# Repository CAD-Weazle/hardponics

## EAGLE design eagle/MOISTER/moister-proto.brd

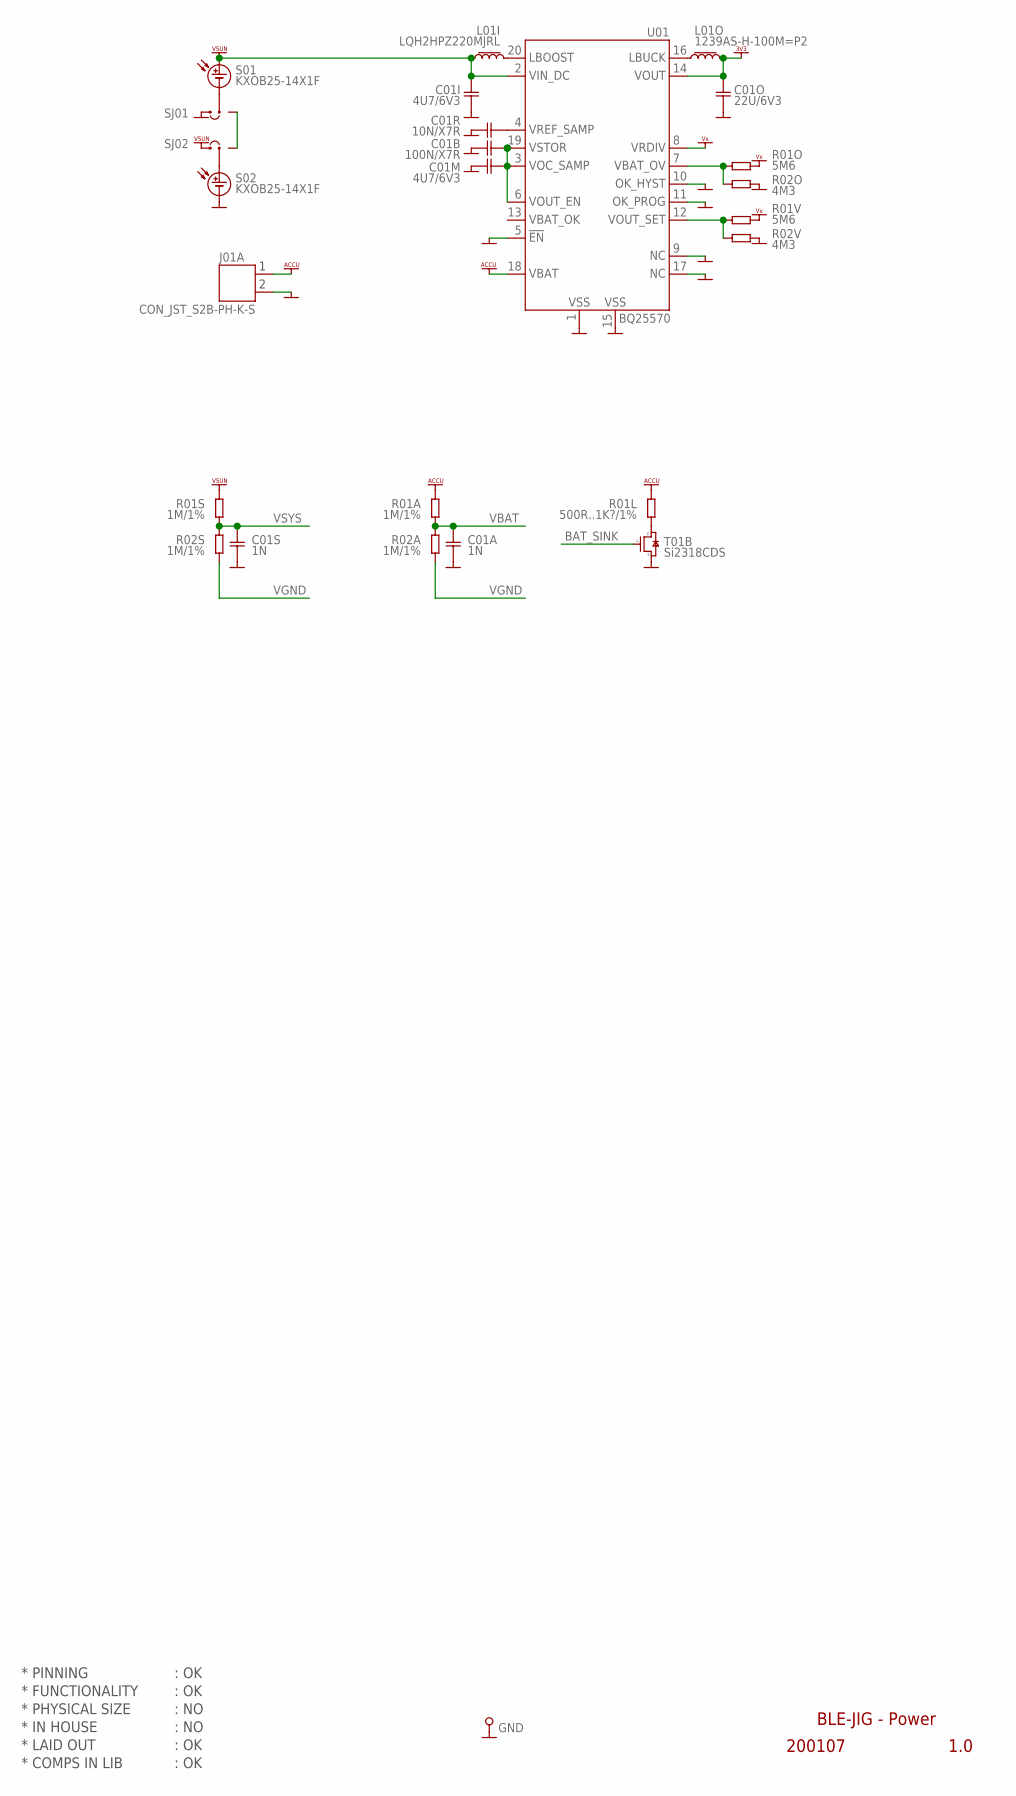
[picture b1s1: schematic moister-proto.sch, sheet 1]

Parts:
C01A, C01S: 1N; CAP0402
C01B: 100N/X7R; CAP0402
C01I, C01M: 4U7/6V3; CAP0402
C01O: 22U/6V3; CAP0402
C01R: 10N/X7R; CAP0402
GND: PIN_TEST; HOLE_PTH_0.8MM
J01A: CON_JST_S2B-PH-K-S
L01I: LQH2HPZ220MJRL; L_1008
L01O: 1239AS-H-100M=P2; L_1008
R01A, R01S, R02A, R02S: 1M/1%; RES0402
R01L: 500R..1K?/1%; RES0603
R01O, R01V: 5M6; RES0402
R02O, R02V: 4M3; RES0402
S01, S02: KXOB25-14X1F
SJ01, SJ02: SJ3SJ3-S; SJ3-S
T01B: Si2318CDS; NFET_SOT23
U01: BQ25570; VQFN20

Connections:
ACCU: J01A.1, R01A.2, R01L.2, U01.18 (18.VBAT)
BAT_SINK: T01B.1 (G1); also elsewhere on the board
GND: C01A.2, C01B.2, C01I.2, C01M.2, C01O.2, C01R.2, C01S.2, GND.1, J01A.2, R02O.2, R02V.2, S02.2, SJ01.1, T01B.2 (S2), U01.1 (1.VSS), U01.5 (5.!EN), U01.9 (9.NC), U01.10 (10.OK_HYST), U01.11 (11.OK_PROG), U01.15 (15.VSS), U01.17 (17.NC), U01.TP (15.VSS), U01.V1 (15.VSS), U01.V2 (15.VSS), U01.V3 (15.VSS), U01.V4 (15.VSS); also elsewhere on the board
unnamed: S01.2, SJ01.2
unnamed: S02.1, SJ02.2
unnamed: SJ01.3, SJ02.3
unnamed: R01L.1, T01B.3 (D3)
unnamed: C01R.1, U01.4 (4.VREF_SAMP)
unnamed: L01I.2, U01.20 (20.LBOOST)
unnamed: L01O.1, U01.16 (16.LBUCK)
VBAT: C01A.1, R01A.1, R02A.2; also elsewhere on the board
VBAT_OV: R01O.2, R02O.1, U01.7 (7.VBAT_OV)
VDD_3V3: C01O.1, L01O.2, U01.14 (14.VOUT); also elsewhere on the board
VGND: R02A.1, R02S.1; also elsewhere on the board
VOUT_SET: R01V.2, R02V.1, U01.12 (12.VOUT_SET)
VSTOR: C01B.1, C01M.1, U01.3 (3.VOC_SAMP), U01.6 (6.VOUT_EN), U01.19 (19.VSTOR)
VSUN: C01I.1, L01I.1, R01S.2, S01.1, SJ02.1, U01.2 (2.VIN_DC)
VSYS: C01S.1, R01S.1, R02S.2; also elsewhere on the board
VX: R01O.1, R01V.1, U01.8 (8.VRDIV)

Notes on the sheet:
* PINNING
* FUNCTIONALITY
* PHYSICAL SIZE
* LAID OUT
* COMPS IN LIB
* IN HOUSE
BLE-JIG - Power
200107
1.0
: OK
: NO

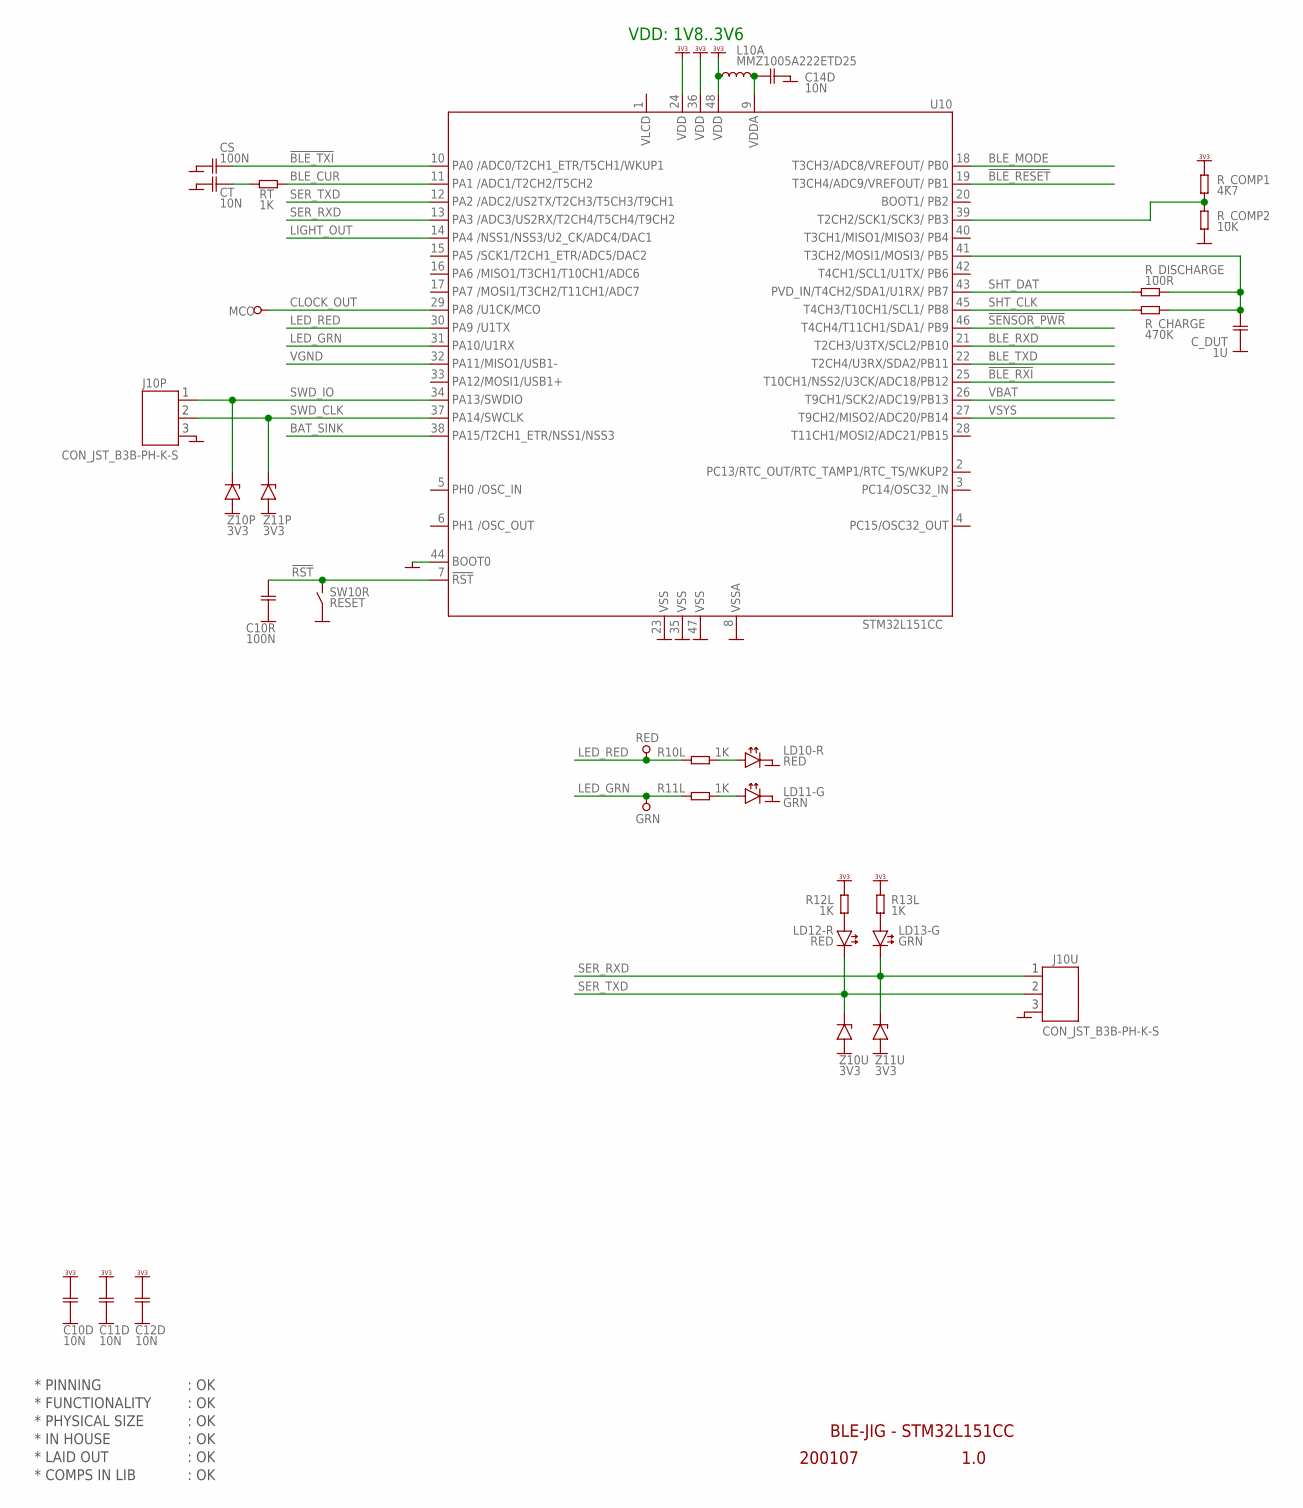
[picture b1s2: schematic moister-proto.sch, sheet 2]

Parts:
C10D, C11D, C12D, C14D: 10N; CAP0402
C10R: 100N; CAP0402
CS: 100N; CAP0805
CT: 10N; CAP0805
C_DUT: 1U; CAP0603
GRN: PIN_TEST_0.6MM; HOLE_PTH_0.6MM
J10P, J10U: CON_JST_B3B-PH-K-S
L10A: MMZ1005A222ETD25; L_0402
LD10-R, LD12-R: RED; LED_SMD_0603
LD11-G, LD13-G: GRN; LED_SMD_0603
MCO: PIN_TEST; HOLE_PTH_0.8MM
R10L, R11L, R12L, R13L: 1K; RES0402
RED: PIN_TEST_0.6MM; HOLE_PTH_0.6MM
RT: 1K; RES0805
R_CHARGE: 470K; RES0603
R_COMP1: 4K7; RES0603
R_COMP2: 10K; RES0603
R_DISCHARGE: 100R; RES0603
SW10R: RESET; SWITCH_PUSHBUTTON_EVP-AVAA1A
U10: STM32L151CC; LQFP48
Z10P, Z10U, Z11P, Z11U: 3V3; ZENER_SOD80

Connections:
!BLE_RESET: U10.19 (19.PB1); also elsewhere on the board
!BLE_RXI: U10.25 (25.PB12); also elsewhere on the board
!BLE_TXI: CS.2, U10.10 (10.PA0); also elsewhere on the board
!RST: C10R.1, SW10R.1 (1-2), U10.7 (7.!RST)
!SENSOR_PWR: U10.46 (46.PB9); also elsewhere on the board
BAT_SINK: U10.38 (38.PA15); also elsewhere on the board
BLE_CUR: RT.1, U10.11 (11.PA1); also elsewhere on the board
BLE_MODE: U10.18 (18.PB0); also elsewhere on the board
BLE_RXD: U10.21 (21.PB10); also elsewhere on the board
BLE_TXD: U10.22 (22.PB11); also elsewhere on the board
CLOCK_OUT: MCO.1, U10.29 (29.PA8)
COMP+: C_DUT.1, R_CHARGE.2, R_DISCHARGE.2, U10.41 (41.PB5)
COMP-: R_COMP1.2, R_COMP2.1, U10.39 (39.PB3)
GND: C10D.2, C10R.2, C11D.2, C12D.2, C14D.2, CS.1, CT.1, C_DUT.2, J10P.3, J10U.3, LD10-R.C, LD11-G.C, R_COMP2.2, SW10R.2 (3-4), U10.8 (8.GND), U10.23 (23.GND), U10.35 (35.GND), U10.44 (44.BOOT0), U10.47 (47.GND), Z10P.1 (A), Z10U.1 (A), Z11P.1 (A), Z11U.1 (A); also elsewhere on the board
LED_GRN: GRN.1, R11L.1, U10.31 (31.PA10)
LED_RED: R10L.1, RED.1, U10.30 (30.PA9)
LIGHT_OUT: U10.14 (14.PA4); also elsewhere on the board
unnamed: CT.2, RT.2
unnamed: LD13-G.A, R13L.2
unnamed: LD12-R.A, R12L.2
unnamed: LD11-G.A, R11L.2
unnamed: LD10-R.A, R10L.2
SER_RXD: J10U.1, LD13-G.C, U10.13 (13.PA3), Z11U.2 (C)
SER_TXD: J10U.2, LD12-R.C, U10.12 (12.PA2), Z10U.2 (C)
SHT_CLK: R_CHARGE.1, U10.45 (45.PB8); also elsewhere on the board
SHT_DAT: R_DISCHARGE.1, U10.43 (43.PB7); also elsewhere on the board
SWD_CLK: J10P.2, U10.37 (37.PA14), Z11P.2 (C)
SWD_IO: J10P.1, U10.34 (34.PA13), Z10P.2 (C)
VBAT: U10.26 (26.PB13); also elsewhere on the board
VDDA: C14D.1, L10A.2, U10.9 (9.VDD)
VDD_3V3: C10D.1, C11D.1, C12D.1, L10A.1, R12L.1, R13L.1, R_COMP1.1, U10.24 (24.VDD), U10.36 (36.VDD), U10.48 (48.VDD); also elsewhere on the board
VGND: U10.32 (32.PA11); also elsewhere on the board
VSYS: U10.27 (27.PB14); also elsewhere on the board

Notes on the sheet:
* PINNING
* FUNCTIONALITY
* PHYSICAL SIZE
* LAID OUT
* COMPS IN LIB
* IN HOUSE
: OK
BLE-JIG - STM32L151CC
200107
1.0
VDD: 1V8..3V6

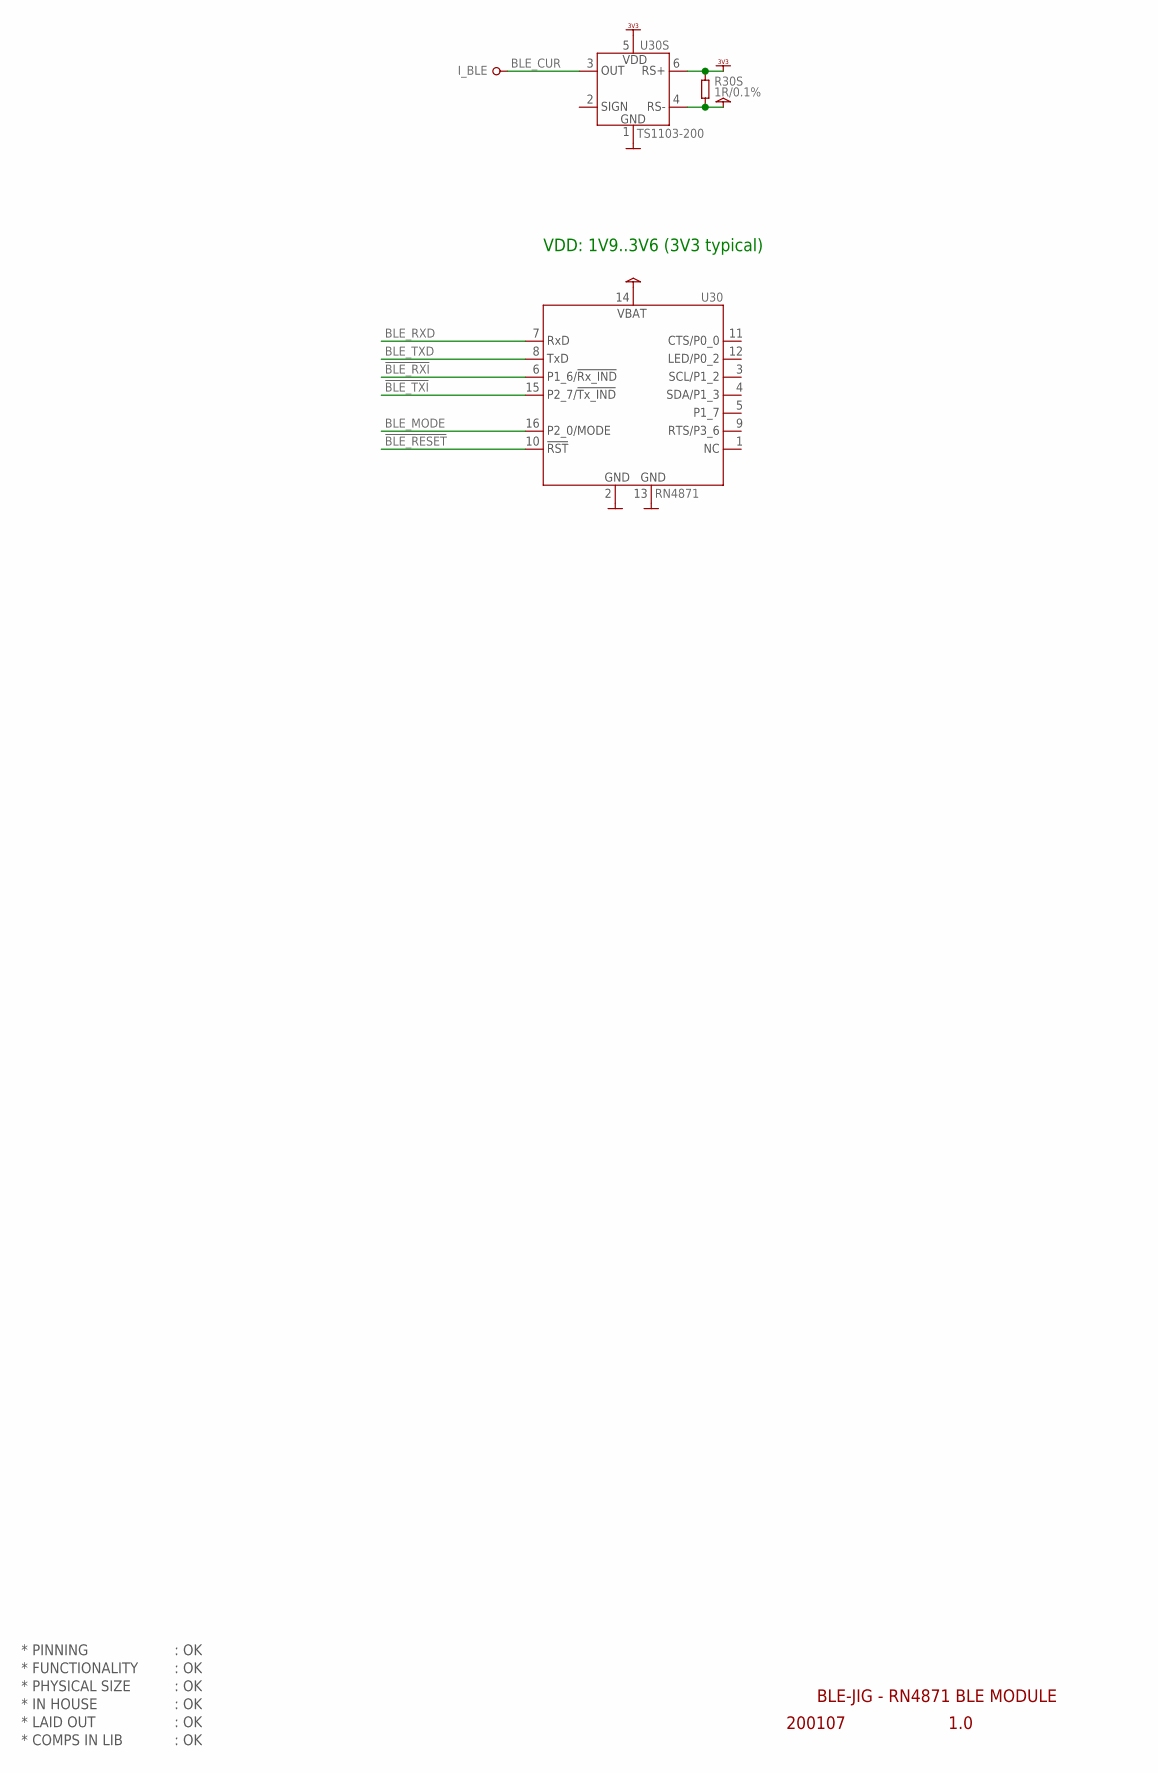
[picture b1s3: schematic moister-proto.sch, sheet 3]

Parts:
I_BLE: PIN_TEST; HOLE_PTH_0.8MM
R30S: 1R/0.1%; RES0603
U30: RN4871
U30S: TS1103-200; SOT23-6

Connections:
!BLE_RESET: U30.10 (10.!RST); also elsewhere on the board
!BLE_RXI: U30.6 (6.P1_6); also elsewhere on the board
!BLE_TXI: U30.15 (15.P2_7); also elsewhere on the board
BLE_CUR: I_BLE.1, U30S.3 (3.OUT); also elsewhere on the board
BLE_MODE: U30.16 (16.P2_0); also elsewhere on the board
BLE_RXD: U30.7 (7.RXD); also elsewhere on the board
BLE_TXD: U30.8 (8.TXD); also elsewhere on the board
GND: U30.2 (2.GND), U30.13 (13.GND), U30S.1 (1.GND); also elsewhere on the board
VCC: R30S.2, U30.14 (14.VBAT), U30S.4 (4.RS-)
VDD_3V3: R30S.1, U30S.5 (5.VDD), U30S.6 (6.RS+); also elsewhere on the board

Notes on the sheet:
* PINNING
* FUNCTIONALITY
* PHYSICAL SIZE
* LAID OUT
* COMPS IN LIB
* IN HOUSE
1.0
BLE-JIG - RN4871 BLE MODULE
200107
: OK
VDD: 1V9..3V6 (3V3 typical)

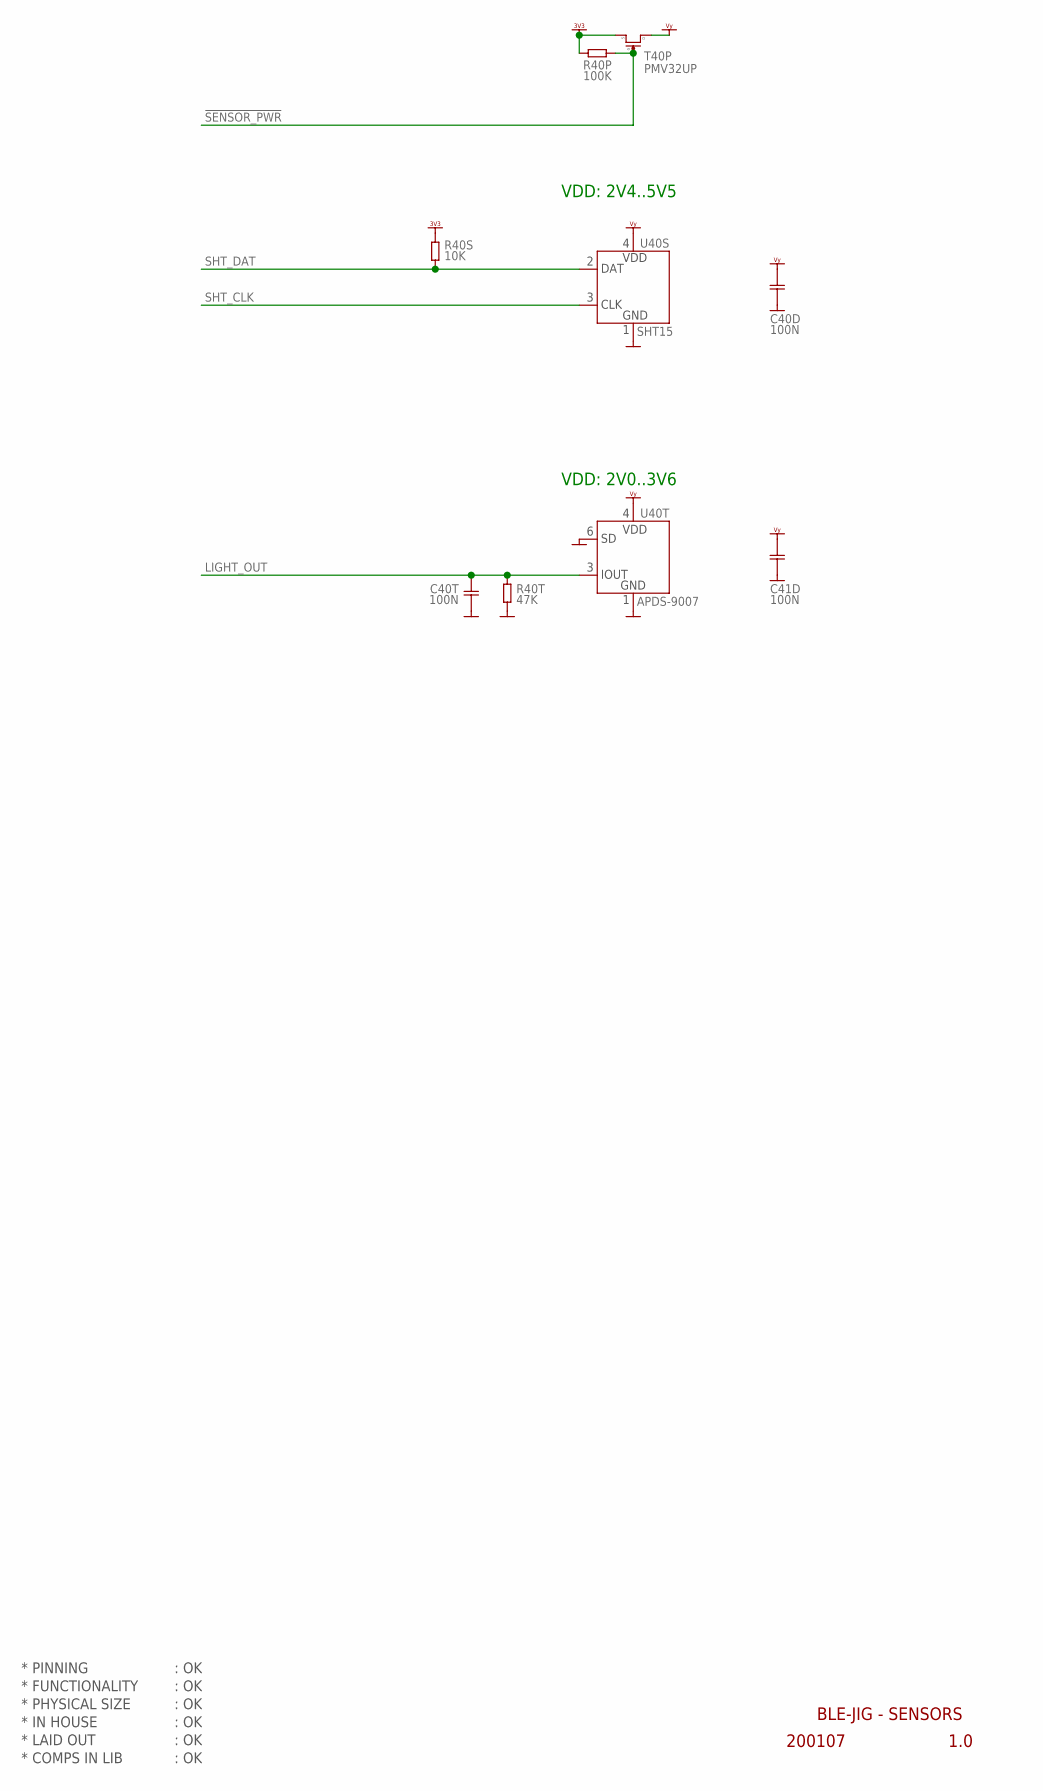
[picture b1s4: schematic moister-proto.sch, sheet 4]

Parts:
C40D, C40T, C41D: 100N; CAP0402
R40P: 100K; RES0402
R40S: 10K; RES0402
R40T: 47K; RES0402
T40P: PMV32UP; PFET_SOT23
U40S: SHT15
U40T: APDS-9007

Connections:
!SENSOR_PWR: R40P.2, T40P.1 (G); also elsewhere on the board
GND: C40D.2, C40T.2, C41D.2, R40T.2, U40S.1 (1.GND), U40T.1 (1.GND), U40T.6 (6.SD); also elsewhere on the board
LIGHT_OUT: C40T.1, R40T.1, U40T.3 (3.IOUT); also elsewhere on the board
SHT_CLK: U40S.3 (3.CLK); also elsewhere on the board
SHT_DAT: R40S.2, U40S.2 (2.DAT); also elsewhere on the board
VDD_3V3: R40P.1, R40S.1, T40P.2 (S); also elsewhere on the board
VY: C40D.1, C41D.1, T40P.3 (D), U40S.4 (4.VDD), U40T.4 (4.VDD)

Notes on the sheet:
* PINNING
* FUNCTIONALITY
* PHYSICAL SIZE
* LAID OUT
* COMPS IN LIB
* IN HOUSE
1.0
BLE-JIG - SENSORS
200107
: OK
VDD: 2V0..3V6
VDD: 2V4..5V5

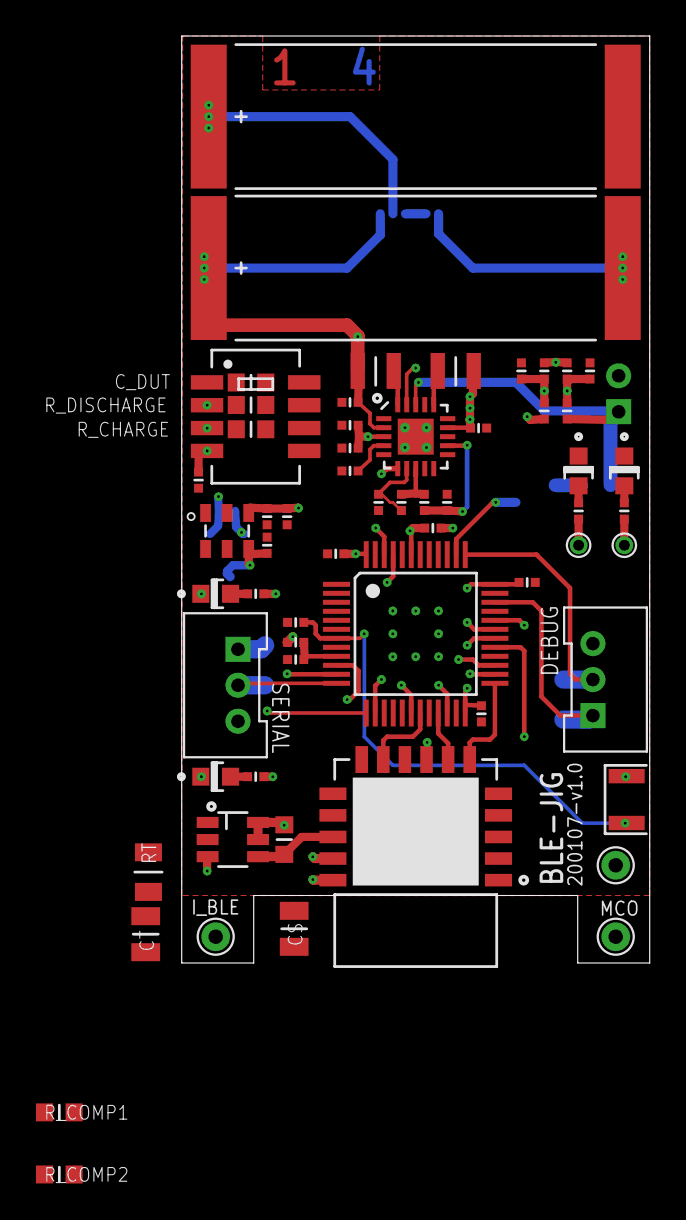
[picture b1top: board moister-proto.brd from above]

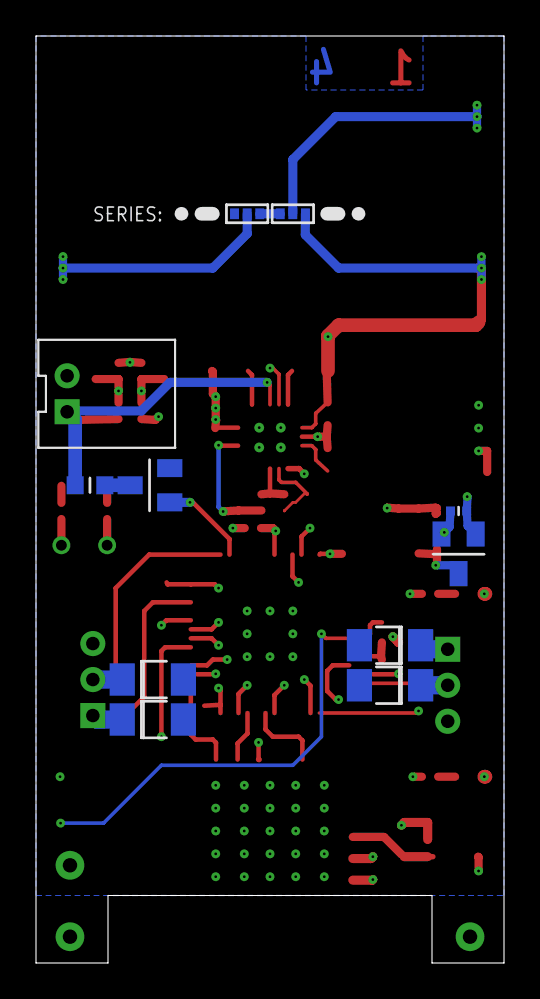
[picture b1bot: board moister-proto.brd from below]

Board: 4 copper layers, 26.0 x 51.5 mm, 72 parts (11 on the bottom side), 48 nets.

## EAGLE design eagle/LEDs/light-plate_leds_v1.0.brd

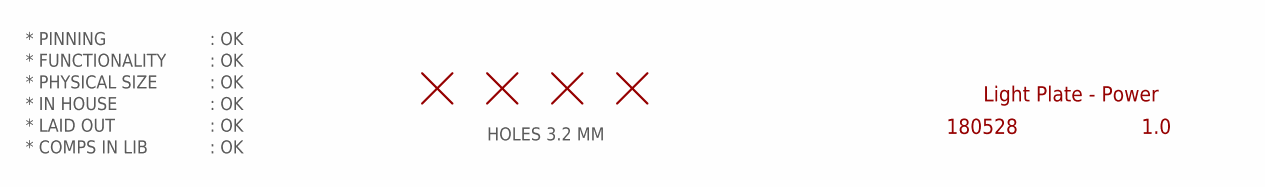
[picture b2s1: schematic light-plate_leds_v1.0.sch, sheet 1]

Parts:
H1, H2, H3, H4: HOLE_NPTH_3.2MM

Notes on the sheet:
* PINNING
* FUNCTIONALITY
* PHYSICAL SIZE
* LAID OUT
* COMPS IN LIB
* IN HOUSE
HOLES 3.2 MM
Light Plate - Power
180528
1.0
: OK

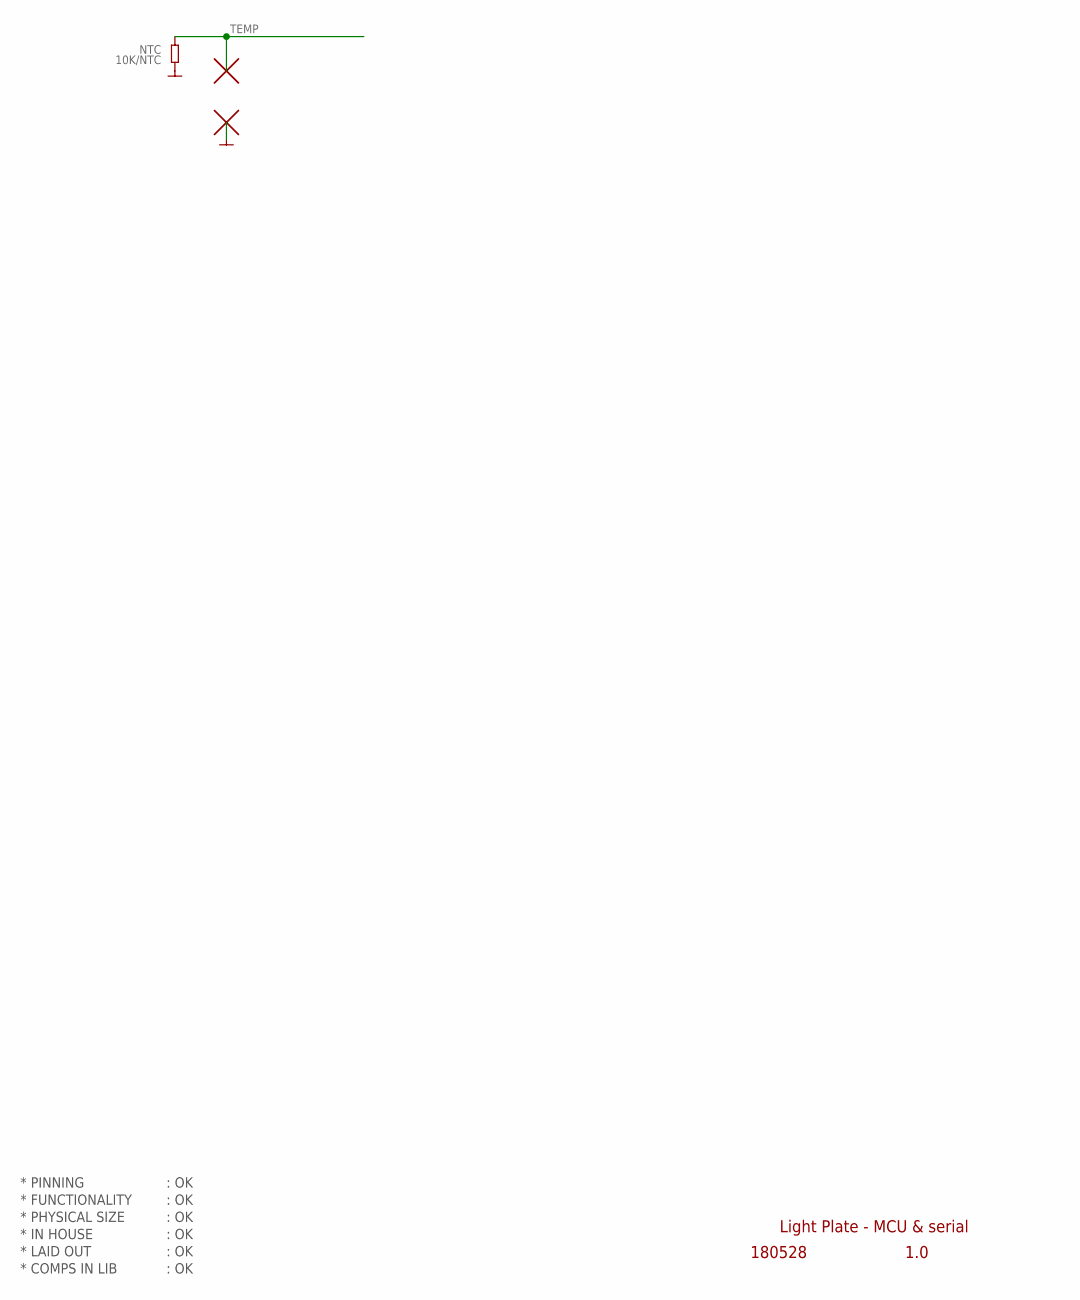
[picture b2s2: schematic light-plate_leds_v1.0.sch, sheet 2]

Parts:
H11, H12: PAD_ROUND_1.6MM
NTC: 10K/NTC; RES0603

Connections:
GND: H11.P, NTC.1
TEMP: H12.P, NTC.2

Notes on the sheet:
* PINNING
* FUNCTIONALITY
* PHYSICAL SIZE
* LAID OUT
* COMPS IN LIB
* IN HOUSE
: OK
Light Plate - MCU & serial
180528
1.0

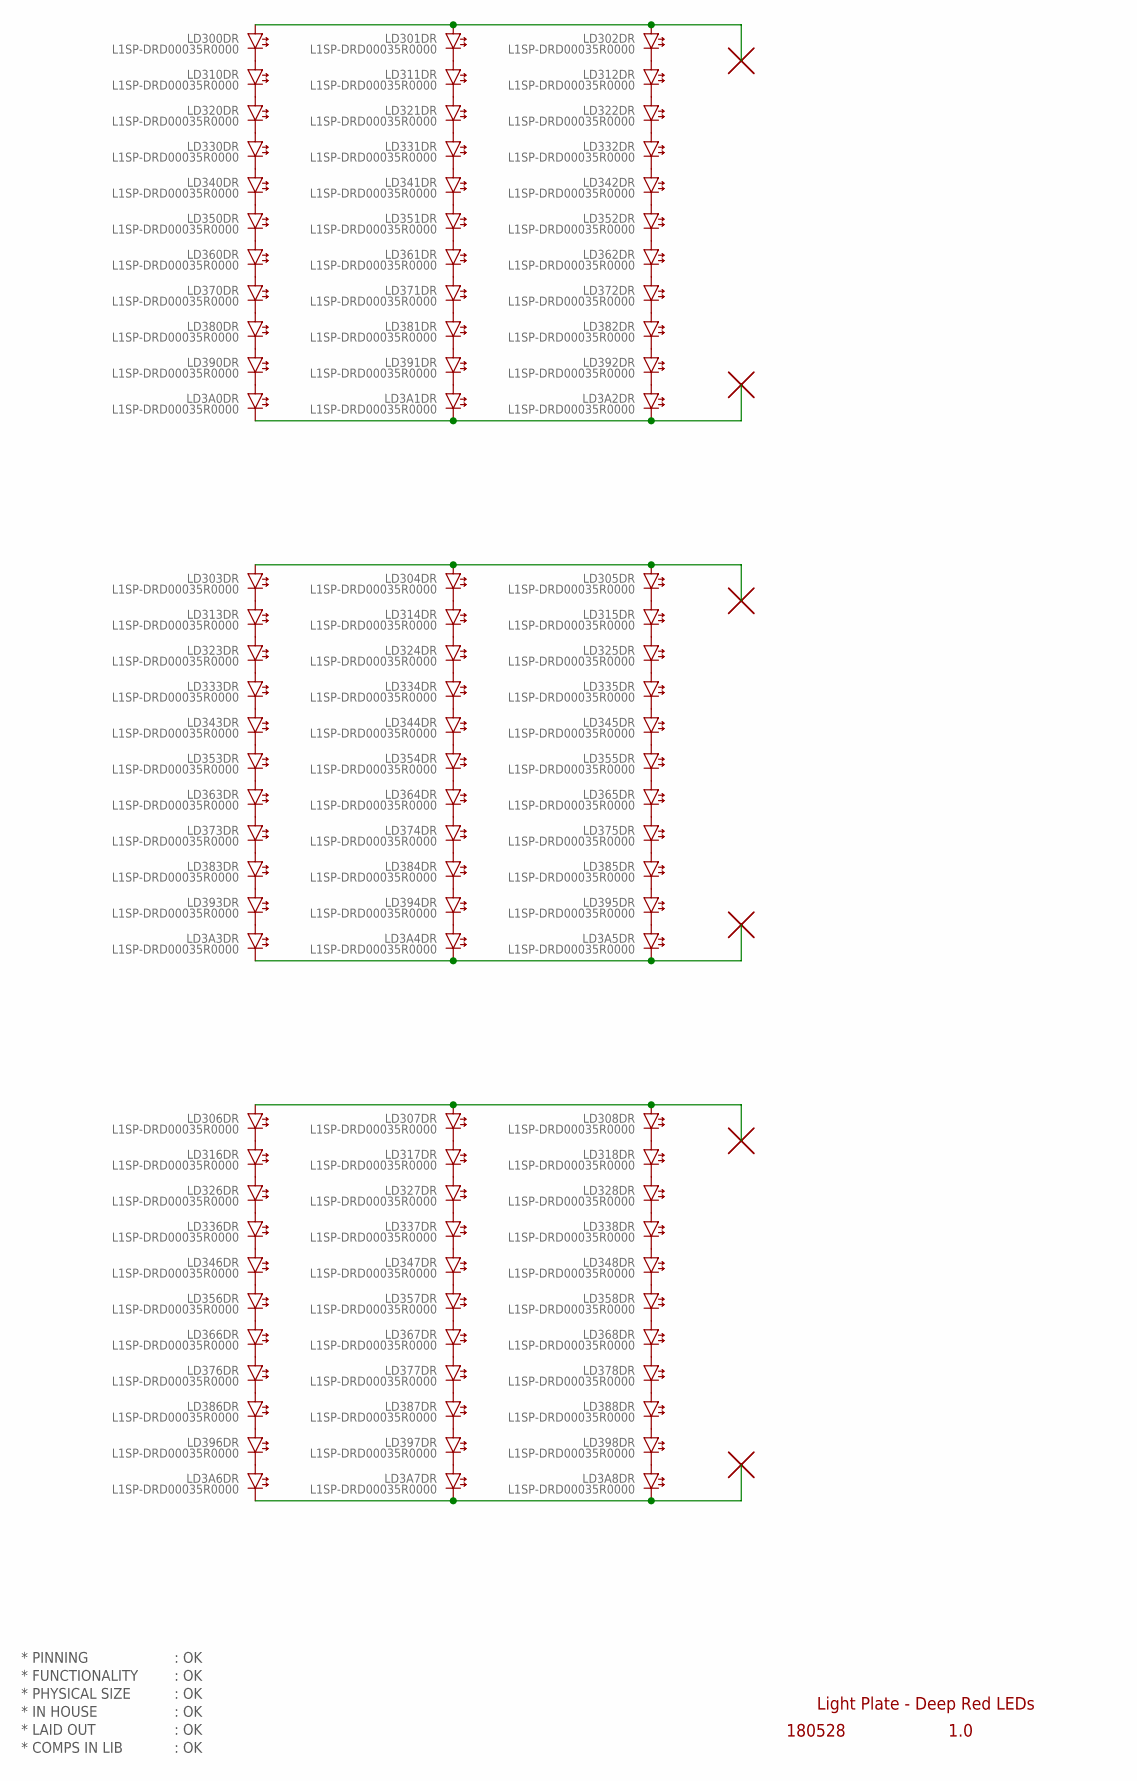
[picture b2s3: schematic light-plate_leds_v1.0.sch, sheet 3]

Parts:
H17, H18, H19, H20, H21, H22: PAD_ROUND_3.2MM
LD3A0DR, LD3A1DR, LD3A2DR, LD3A3DR, LD3A4DR, LD3A5DR, LD3A6DR, LD3A7DR, LD3A8DR, LD300DR, LD301DR, LD302DR, LD303DR, LD304DR, LD305DR, LD306DR, LD307DR, LD308DR, LD310DR, LD311DR, LD312DR, LD313DR, LD314DR, LD315DR, LD316DR, LD317DR, LD318DR, LD320DR, LD321DR, LD322DR, LD323DR, LD324DR, LD325DR, LD326DR, LD327DR, LD328DR, LD330DR, LD331DR, LD332DR, LD333DR, LD334DR, LD335DR, LD336DR, LD337DR, LD338DR, LD340DR, LD341DR, LD342DR, LD343DR, LD344DR, LD345DR, LD346DR, LD347DR, LD348DR, LD350DR, LD351DR, LD352DR, LD353DR, LD354DR, LD355DR, LD356DR, LD357DR, LD358DR, LD360DR, LD361DR, LD362DR, LD363DR, LD364DR, LD365DR, LD366DR, LD367DR, LD368DR, LD370DR, LD371DR, LD372DR, LD373DR, LD374DR, LD375DR, LD376DR, LD377DR, LD378DR, LD380DR, LD381DR, LD382DR, LD383DR, LD384DR, LD385DR, LD386DR, LD387DR, LD388DR, LD390DR, LD391DR, LD392DR, LD393DR, LD394DR, LD395DR, LD396DR, LD397DR, LD398DR: L1SP-DRD00035R0000; LED_SMD_SUNPLUS35_REVERSED

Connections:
unnamed: LD300DR.A (-), LD310DR.C (+)
unnamed: LD310DR.A (-), LD320DR.C (+)
unnamed: LD320DR.A (-), LD330DR.C (+)
unnamed: LD330DR.A (-), LD340DR.C (+)
unnamed: LD340DR.A (-), LD350DR.C (+)
unnamed: LD350DR.A (-), LD360DR.C (+)
unnamed: LD360DR.A (-), LD370DR.C (+)
unnamed: LD370DR.A (-), LD380DR.C (+)
unnamed: LD380DR.A (-), LD390DR.C (+)
unnamed: LD3A0DR.C (+), LD390DR.A (-)
unnamed: LD301DR.A (-), LD311DR.C (+)
unnamed: LD311DR.A (-), LD321DR.C (+)
unnamed: LD321DR.A (-), LD331DR.C (+)
unnamed: LD331DR.A (-), LD341DR.C (+)
unnamed: LD341DR.A (-), LD351DR.C (+)
unnamed: LD351DR.A (-), LD361DR.C (+)
unnamed: LD361DR.A (-), LD371DR.C (+)
unnamed: LD371DR.A (-), LD381DR.C (+)
unnamed: LD381DR.A (-), LD391DR.C (+)
unnamed: LD3A1DR.C (+), LD391DR.A (-)
unnamed: LD302DR.A (-), LD312DR.C (+)
unnamed: LD312DR.A (-), LD322DR.C (+)
unnamed: LD322DR.A (-), LD332DR.C (+)
unnamed: LD332DR.A (-), LD342DR.C (+)
unnamed: LD342DR.A (-), LD352DR.C (+)
unnamed: LD352DR.A (-), LD362DR.C (+)
unnamed: LD362DR.A (-), LD372DR.C (+)
unnamed: LD372DR.A (-), LD382DR.C (+)
unnamed: LD382DR.A (-), LD392DR.C (+)
unnamed: LD3A2DR.C (+), LD392DR.A (-)
unnamed: LD303DR.A (-), LD313DR.C (+)
unnamed: LD313DR.A (-), LD323DR.C (+)
unnamed: LD323DR.A (-), LD333DR.C (+)
unnamed: LD333DR.A (-), LD343DR.C (+)
unnamed: LD343DR.A (-), LD353DR.C (+)
unnamed: LD353DR.A (-), LD363DR.C (+)
unnamed: LD363DR.A (-), LD373DR.C (+)
unnamed: LD373DR.A (-), LD383DR.C (+)
unnamed: LD383DR.A (-), LD393DR.C (+)
unnamed: LD3A3DR.C (+), LD393DR.A (-)
unnamed: LD304DR.A (-), LD314DR.C (+)
unnamed: LD314DR.A (-), LD324DR.C (+)
unnamed: LD324DR.A (-), LD334DR.C (+)
unnamed: LD334DR.A (-), LD344DR.C (+)
unnamed: LD344DR.A (-), LD354DR.C (+)
unnamed: LD354DR.A (-), LD364DR.C (+)
unnamed: LD364DR.A (-), LD374DR.C (+)
unnamed: LD374DR.A (-), LD384DR.C (+)
unnamed: LD384DR.A (-), LD394DR.C (+)
unnamed: LD3A4DR.C (+), LD394DR.A (-)
unnamed: LD305DR.A (-), LD315DR.C (+)
unnamed: LD315DR.A (-), LD325DR.C (+)
unnamed: LD325DR.A (-), LD335DR.C (+)
unnamed: LD335DR.A (-), LD345DR.C (+)
unnamed: LD345DR.A (-), LD355DR.C (+)
unnamed: LD355DR.A (-), LD365DR.C (+)
unnamed: LD365DR.A (-), LD375DR.C (+)
unnamed: LD375DR.A (-), LD385DR.C (+)
unnamed: LD385DR.A (-), LD395DR.C (+)
unnamed: LD3A5DR.C (+), LD395DR.A (-)
unnamed: LD306DR.A (-), LD316DR.C (+)
unnamed: LD316DR.A (-), LD326DR.C (+)
unnamed: LD326DR.A (-), LD336DR.C (+)
unnamed: LD336DR.A (-), LD346DR.C (+)
unnamed: LD346DR.A (-), LD356DR.C (+)
unnamed: LD356DR.A (-), LD366DR.C (+)
unnamed: LD366DR.A (-), LD376DR.C (+)
unnamed: LD376DR.A (-), LD386DR.C (+)
unnamed: LD386DR.A (-), LD396DR.C (+)
unnamed: LD3A6DR.C (+), LD396DR.A (-)
unnamed: LD307DR.A (-), LD317DR.C (+)
unnamed: LD317DR.A (-), LD327DR.C (+)
unnamed: LD327DR.A (-), LD337DR.C (+)
unnamed: LD337DR.A (-), LD347DR.C (+)
unnamed: LD347DR.A (-), LD357DR.C (+)
unnamed: LD357DR.A (-), LD367DR.C (+)
unnamed: LD367DR.A (-), LD377DR.C (+)
unnamed: LD377DR.A (-), LD387DR.C (+)
unnamed: LD387DR.A (-), LD397DR.C (+)
unnamed: LD3A7DR.C (+), LD397DR.A (-)
unnamed: LD308DR.A (-), LD318DR.C (+)
unnamed: LD318DR.A (-), LD328DR.C (+)
unnamed: LD328DR.A (-), LD338DR.C (+)
unnamed: LD338DR.A (-), LD348DR.C (+)
unnamed: LD348DR.A (-), LD358DR.C (+)
unnamed: LD358DR.A (-), LD368DR.C (+)
unnamed: LD368DR.A (-), LD378DR.C (+)
unnamed: LD378DR.A (-), LD388DR.C (+)
unnamed: LD388DR.A (-), LD398DR.C (+)
unnamed: LD3A8DR.C (+), LD398DR.A (-)
unnamed: H18.P, LD3A0DR.A (-), LD3A1DR.A (-), LD3A2DR.A (-)
unnamed: H20.P, LD3A3DR.A (-), LD3A4DR.A (-), LD3A5DR.A (-)
unnamed: H22.P, LD3A6DR.A (-), LD3A7DR.A (-), LD3A8DR.A (-)
unnamed: H17.P, LD300DR.C (+), LD301DR.C (+), LD302DR.C (+)
unnamed: H19.P, LD303DR.C (+), LD304DR.C (+), LD305DR.C (+)
unnamed: H21.P, LD306DR.C (+), LD307DR.C (+), LD308DR.C (+)

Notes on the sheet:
* PINNING
* FUNCTIONALITY
* PHYSICAL SIZE
* LAID OUT
* COMPS IN LIB
* IN HOUSE
: OK
Light Plate - Deep Red LEDs
1.0
180528
